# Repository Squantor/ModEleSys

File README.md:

# ModEleSys
This repository contains a modular system for electronics projects. It encompasses a backplane of which a few variants exist. Next to that there are various modules that are plugged into this backplane. These modules are 4 by 5 cm in size and the current backplane can contain 4 of them in a 2 by 2 grid. 
These modules come in different sizes, a 1by1 module occupies just one spot on the backplane, the 2by1 and 1by2 module occupy two spots and are for larger projects. Hypothetically there would also be a 2by2 module also but if you have that, why do you need a backplane?
If you use stackable headers for the modules, in principle you could stack multiple modules on top of eachother.

There are various modules available with the following functions:

* Power supply in a few different variants
* Microcontroller boards in a few different variants

These are "generic" building blocks so they can be used in many different projects. Project specific modules usually are owned by the projects themselves. Below is a non exhaustive list of projects using this system:
* [Ultra pure oscillator](https://github.com/Squantor/Metrology/tree/master/electronics/oscillator_variant_2) and [notch filter](https://github.com/Squantor/Metrology/tree/master/electronics/notch_filter)

I intend to use this system for many projects I have in mind.

## Structure
* [electronics](electronics/README.md) contains all the electronic hardware
* [software](software/README.md) contains all the software used in the project. Mostly contains examples for the microcontroller boards using this system.
* [mechanical](mechanical/README.md) contains all the CAD drawings, mostly 3d printable objects.
* [documentation](documentation/README.md) contains more in depth information and examples using this system.
## Cloning
This repository makes extensive use of submodules, use ```git clone --recurse-submodules https://github.com/Squantor/generic_project_template.git``` to clone everything in one go.

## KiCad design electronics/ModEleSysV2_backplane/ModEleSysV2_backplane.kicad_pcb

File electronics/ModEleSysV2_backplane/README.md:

# 10 by 10 cm aluminium box backplane with 30 pin DIN41612 connectors
10 by 10 cm aluminium box backplane  capable of fitting 4 5*4cm modules
## TODO's
Still some things need to be done:
* Review with one night in between
* Production
* Assemble
* Test & characterise
* update Readme.md with pictures and BOM
## BOM
* Search on ebay/aliexpress for a 10 by 10 by 5 extruded aluminium box.
* Momentary push pull switch (Todo LCSC partnumber)
* Angled LED
* Miscellanious passives
## Pictures

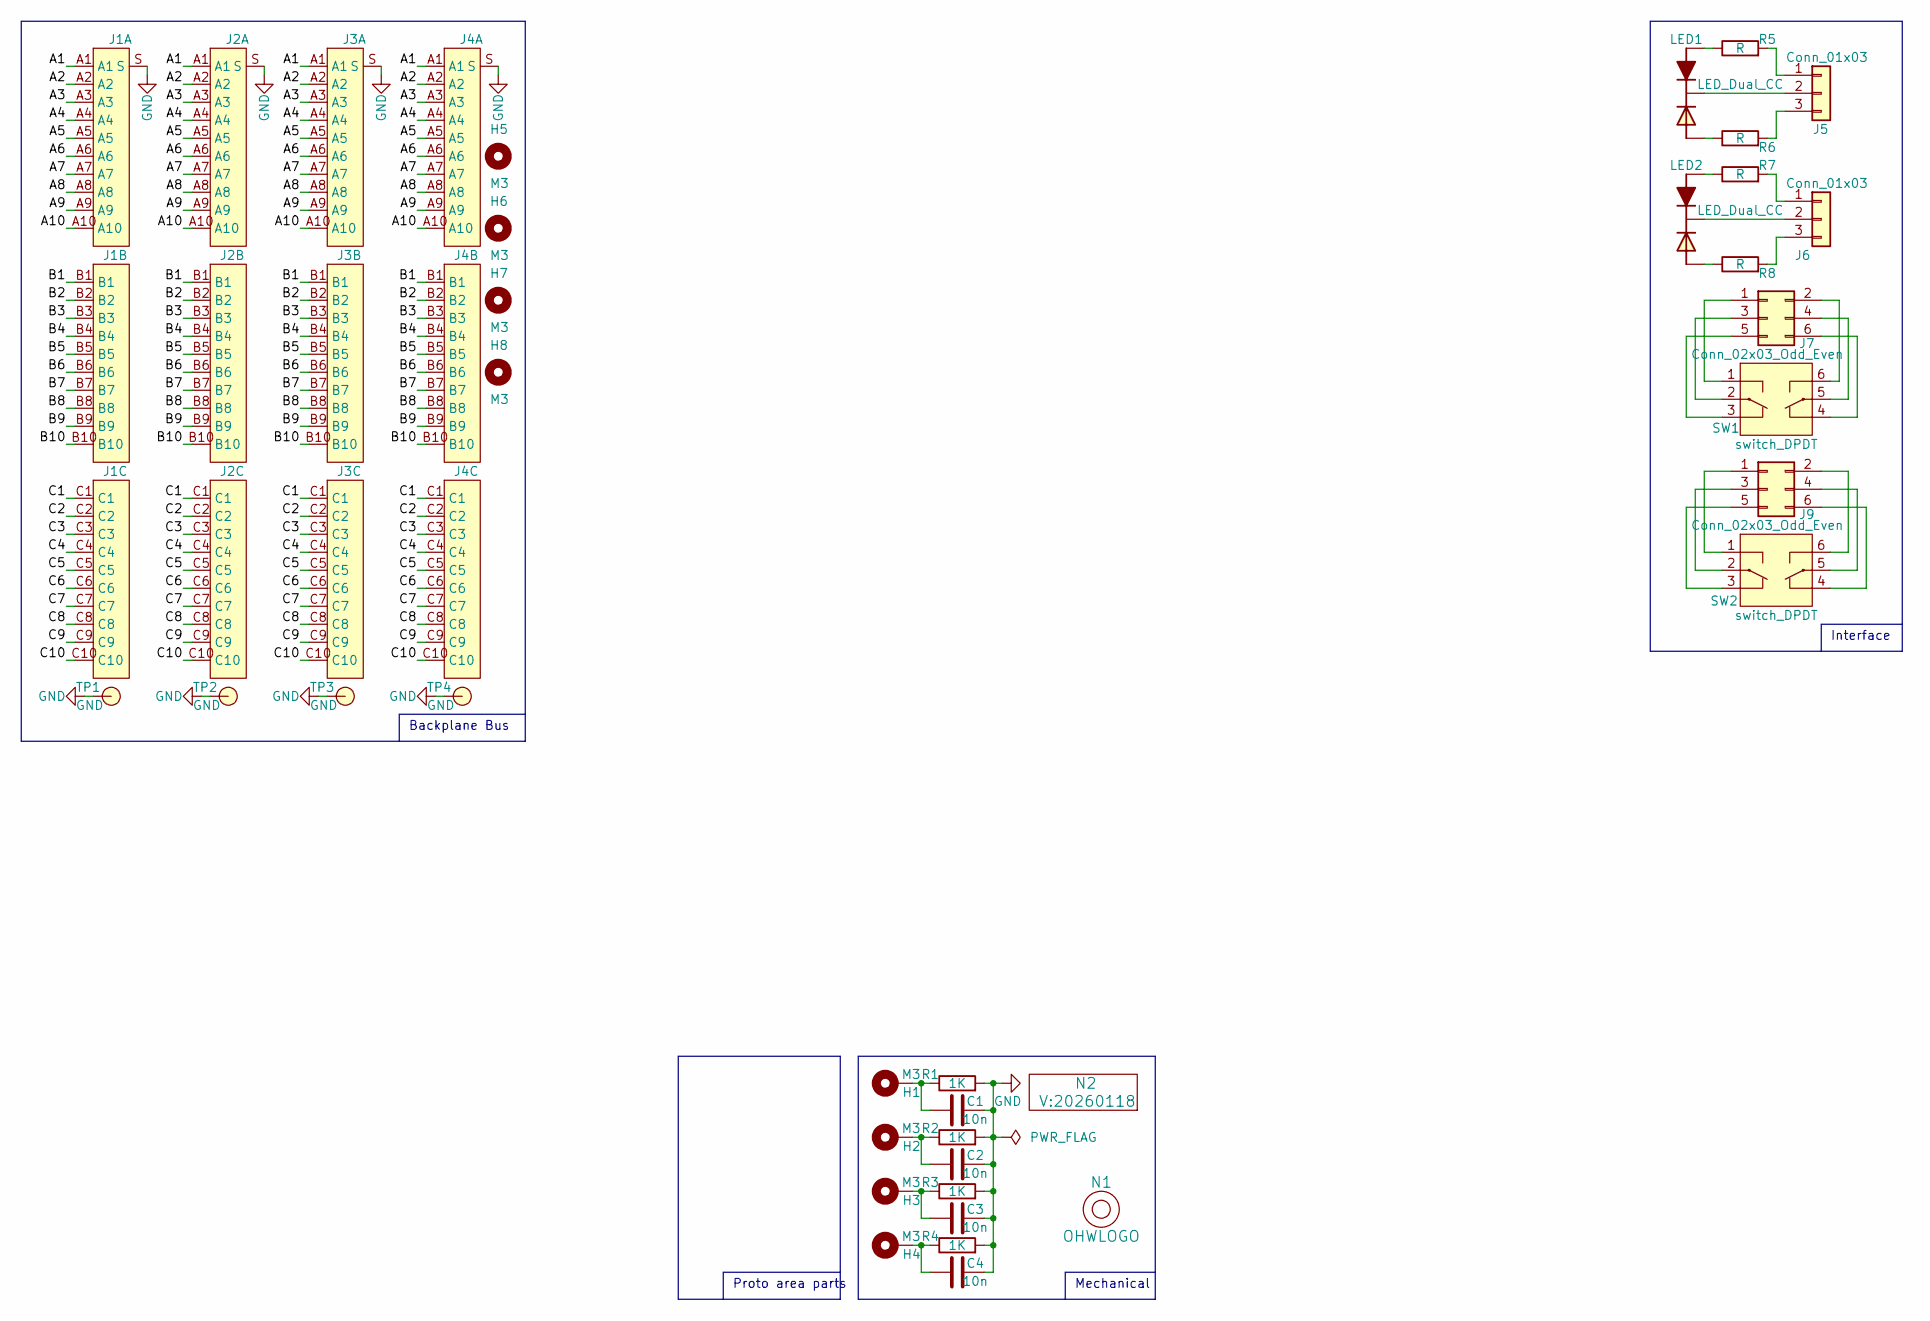
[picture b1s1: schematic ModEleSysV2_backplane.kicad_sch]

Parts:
C1, C2, C3, C4: 10n; C_0805+0603
H1, H2, H3, H4, H5, H6, H7, H8: M3; MountingHole_3.2mm_M3_Pad_Via
J1, J2, J3, J4: DIN41612_C3_3x10_Female_Vertical_THT_shields
J5, J6: Conn_01x03; JST_PH_B3B-PH-K_1x03_P2.00mm_Vertical
J7, J9: Conn_02x03_Odd_Even; DLL-XHY-6A
LED1, LED2: LED_Dual_CC; LED_DUAL_TH245_90deg
N1: OHWLOGO; OSHW-Symbol_6.7x6mm_SilkScreen
N2: V:20260118; Label_Generic
R1, R2, R3, R4: 1K; R_0805+0603
R5, R6, R7, R8: R; R_0603_hand
SW1, SW2: switch_DPDT; PS-22F02
TP1, TP2, TP3, TP4: GND; TestPoint_hole_H05R10

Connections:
/A1: J1.A1, J2.A1, J3.A1, J4.A1
/A2: J1.A2, J2.A2, J3.A2, J4.A2
/A3: J1.A3, J2.A3, J3.A3, J4.A3
/A4: J1.A4, J2.A4, J3.A4, J4.A4
/A5: J1.A5, J2.A5, J3.A5, J4.A5
/A6: J1.A6, J2.A6, J3.A6, J4.A6
/A7: J1.A7, J2.A7, J3.A7, J4.A7
/A8: J1.A8, J2.A8, J3.A8, J4.A8
/A9: J1.A9, J2.A9, J3.A9, J4.A9
/A10: J1.A10, J2.A10, J3.A10, J4.A10
/B1: J1.B1, J2.B1, J3.B1, J4.B1
/B2: J1.B2, J2.B2, J3.B2, J4.B2
/B3: J1.B3, J2.B3, J3.B3, J4.B3
/B4: J1.B4, J2.B4, J3.B4, J4.B4
/B5: J1.B5, J2.B5, J3.B5, J4.B5
/B6: J1.B6, J2.B6, J3.B6, J4.B6
/B7: J1.B7, J2.B7, J3.B7, J4.B7
/B8: J1.B8, J2.B8, J3.B8, J4.B8
/B9: J1.B9, J2.B9, J3.B9, J4.B9
/B10: J1.B10, J2.B10, J3.B10, J4.B10
/C1: J1.C1, J2.C1, J3.C1, J4.C1
/C2: J1.C2, J2.C2, J3.C2, J4.C2
/C3: J1.C3, J2.C3, J3.C3, J4.C3
/C4: J1.C4, J2.C4, J3.C4, J4.C4
/C5: J1.C5, J2.C5, J3.C5, J4.C5
/C6: J1.C6, J2.C6, J3.C6, J4.C6
/C7: J1.C7, J2.C7, J3.C7, J4.C7
/C8: J1.C8, J2.C8, J3.C8, J4.C8
/C9: J1.C9, J2.C9, J3.C9, J4.C9
/C10: J1.C10, J2.C10, J3.C10, J4.C10
GND: C1.2, C2.2, C3.2, C4.2, J1.S, J2.S, J3.S, J4.S, R1.2, R2.2, R3.2, R4.2, TP1.1, TP2.1, TP3.1, TP4.1
unnamed: C1.1, H1.1, R1.1
unnamed: C2.1, H2.1, R2.1
unnamed: C3.1, H3.1, R3.1
unnamed: C4.1, H4.1, R4.1
unnamed: J5.1, R5.2
unnamed: J5.2, LED1.2 (C)
unnamed: J5.3, R6.2
unnamed: J6.1, R7.2
unnamed: J6.2, LED2.2 (C)
unnamed: J6.3, R8.2
unnamed: J7.1, SW1.1 (SW1_P1)
unnamed: J7.2, SW1.6 (SW2_P2)
unnamed: J7.3, SW1.2 (SW1_C1)
unnamed: J7.4, SW1.5 (SW2_C1)
unnamed: J7.5, SW1.3 (SW1_P2)
unnamed: J7.6, SW1.4 (SW2_P2)
unnamed: J9.1, SW2.1 (SW1_P1)
unnamed: J9.2, SW2.6 (SW2_P2)
unnamed: J9.3, SW2.2 (SW1_C1)
unnamed: J9.4, SW2.5 (SW2_C1)
unnamed: J9.5, SW2.3 (SW1_P2)
unnamed: J9.6, SW2.4 (SW2_P2)
unnamed: LED1.1 (A1), R5.1
unnamed: LED1.3 (A2), R6.1
unnamed: LED2.1 (A1), R7.1
unnamed: LED2.3 (A2), R8.1

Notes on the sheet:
Proto area parts
Mechanical
Interface
Backplane Bus

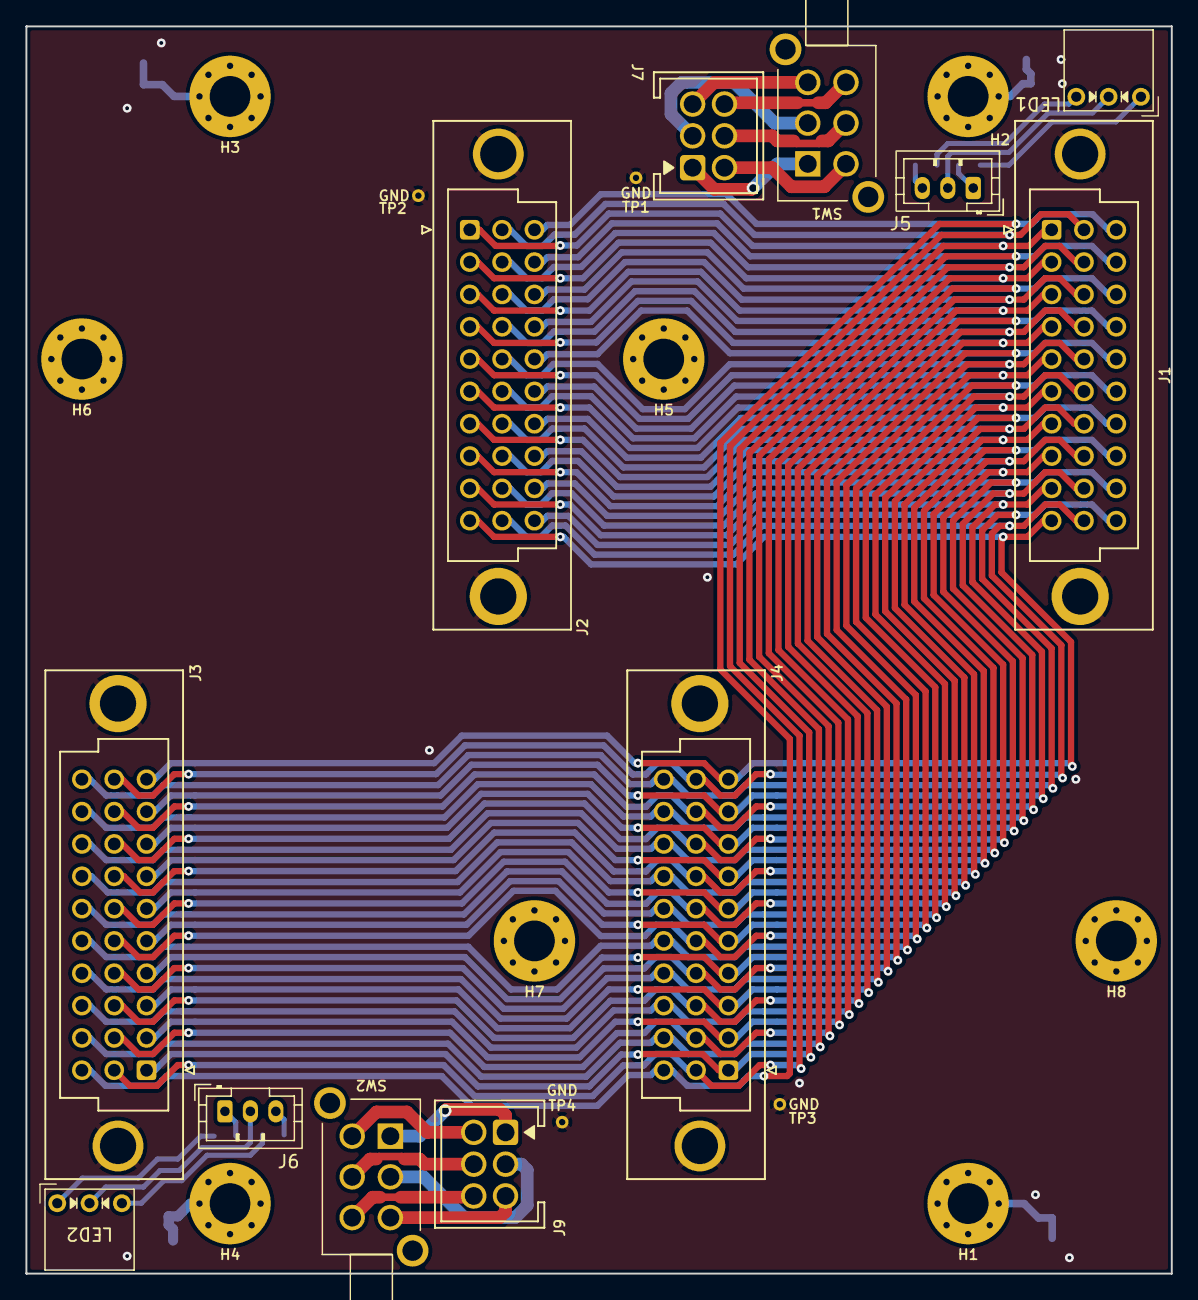
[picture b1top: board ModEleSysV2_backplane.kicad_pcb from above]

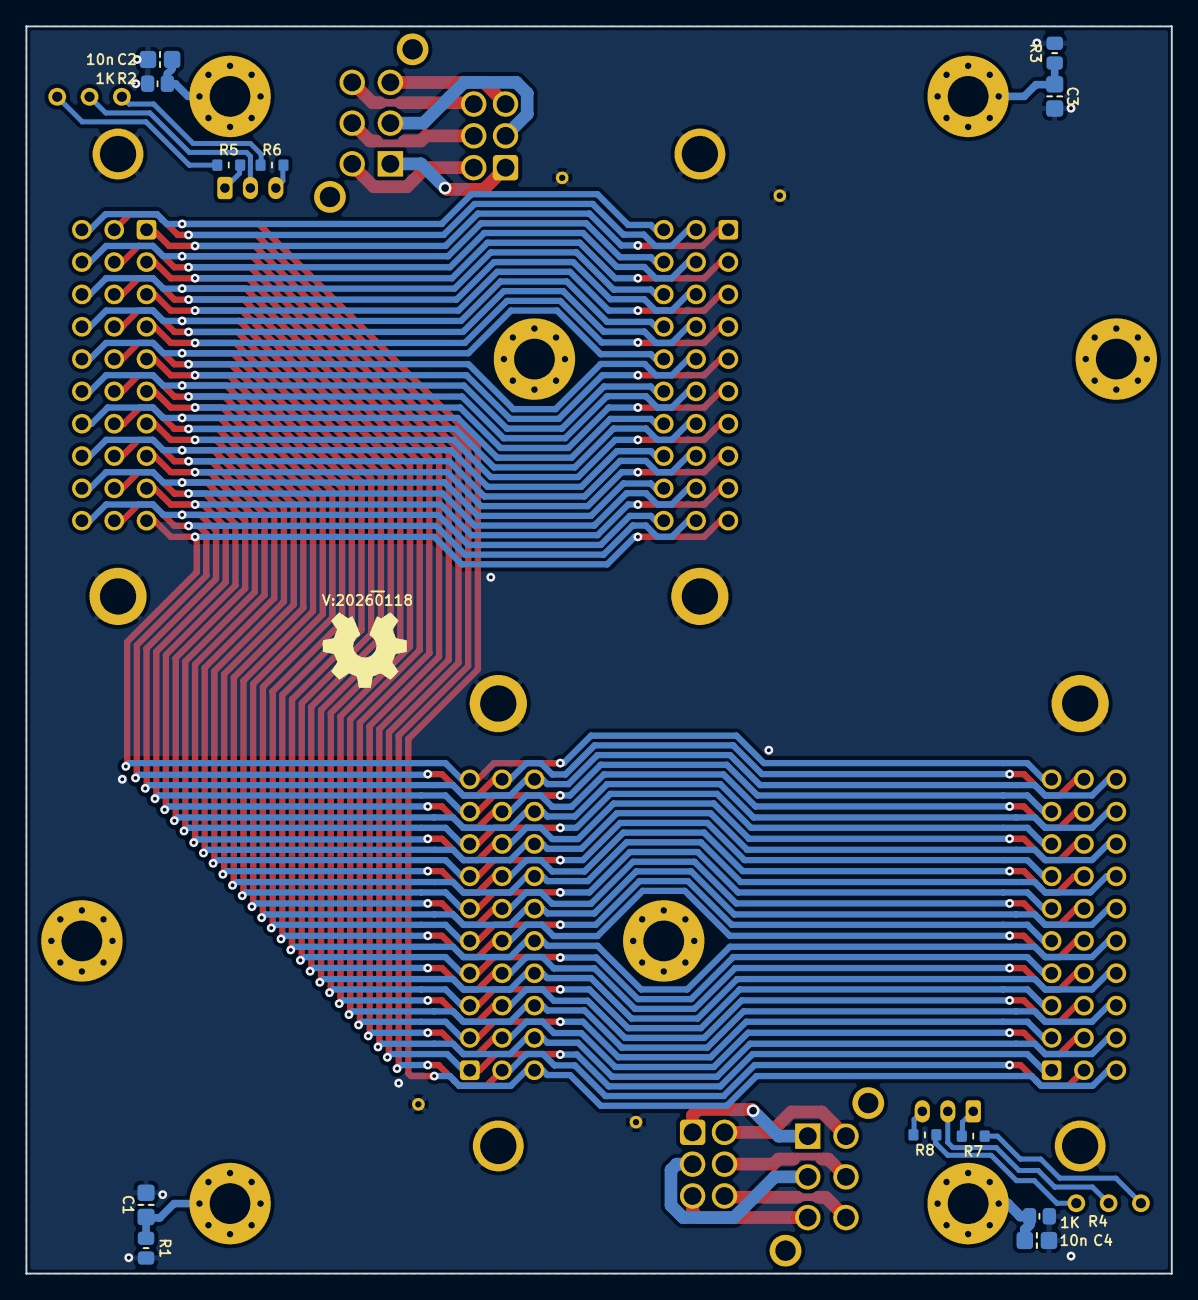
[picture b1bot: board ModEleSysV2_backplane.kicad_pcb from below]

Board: 2 copper layers, 90.0 x 98.0 mm, 38 parts (14 on the bottom side), 57 nets.

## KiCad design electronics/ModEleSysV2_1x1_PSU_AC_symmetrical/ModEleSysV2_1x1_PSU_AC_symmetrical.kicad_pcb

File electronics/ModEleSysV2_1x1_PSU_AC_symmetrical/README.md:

# ModEleSys V2 AC symmetrical powersupply project
This is a ModEleSys V2 module that takes an AC power input and changes this into symmetrical power on de +V and -V pins.
## TODO's
Still some things need to be done:
* Produce at Aisler/Oshpark/JLCPCB
* Assemble
* Test & characterise
* update Readme.md with pictures and BOM
## BOM
* D2PAK LM317/337
## Pictures
TODO

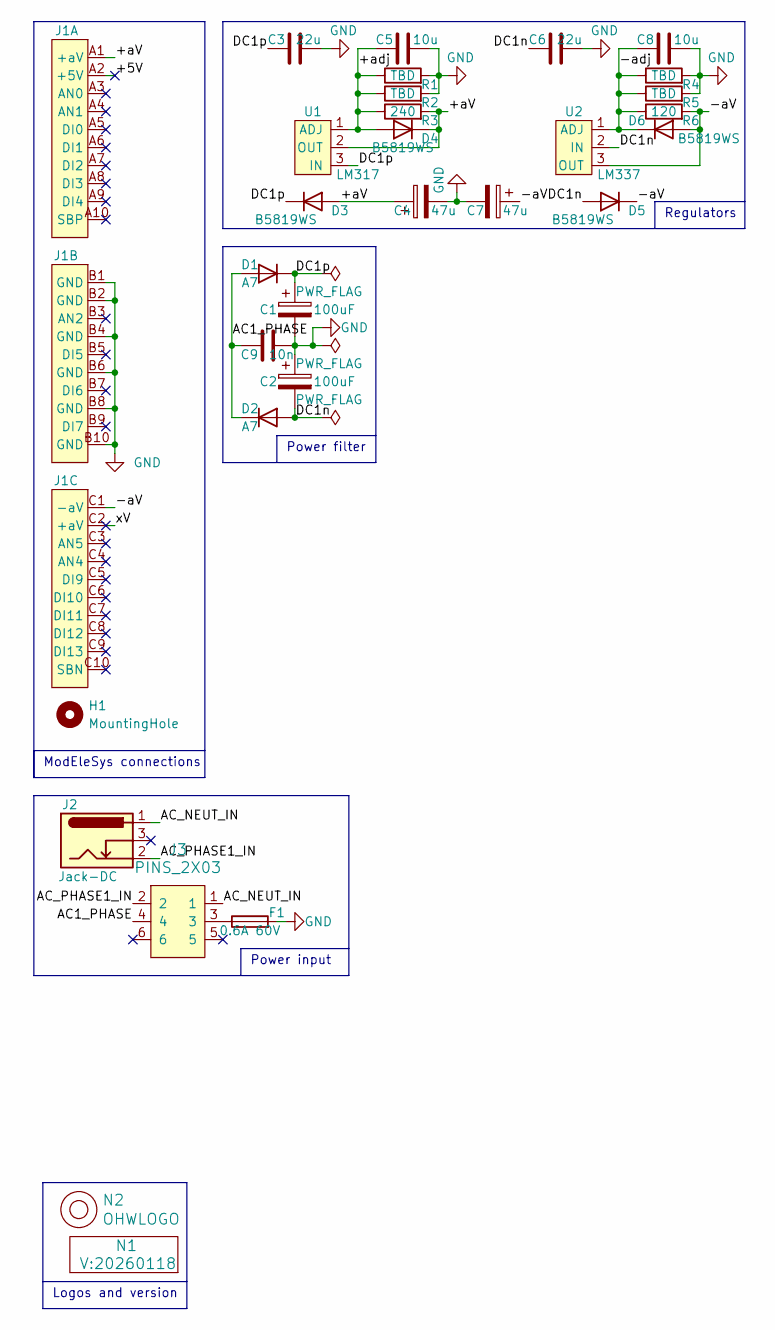
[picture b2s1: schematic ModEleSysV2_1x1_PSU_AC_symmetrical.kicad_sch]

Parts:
C1, C2: 100uF; C-050-100-elco-lying
C3, C6: 22u; C_1206_0805
C4, C7: 47u; C-025-065-elco
C5, C8: 10u; C_0805+0603
C9: 10n; C_0805+0603
D1, D2: A7; SOD-123F-hand
D3, D4, D5, D6: B5819WS; SOD-323-nexperia-hand
F1: 0.6A 60V; F_1812-bourns
H1: MountingHole; MountingHole_3.2mm_M3_Pad_Via
J1: DIN41612_R3_3x10_Male_Vertical_THT
J2: Jack-DC; BarrelJack_Horizontal_Holed
J3: PINS_2X03; DLL-XHY-6A
N1: V:20260118; Label_Generic
N2: OHWLOGO; OSHW-Symbol_6.7x6mm_SilkScreen
R1, R2, R4, R5: TBD; R_0805+0603
R3: 240; R_0805+0603
R6: 120; R_0805+0603
U1: LM317; SOT-223
U2: LM337; SOT-223

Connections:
/+5V: J1.A2 (+5V)
/+aV: C4.1, D3.2 (A), D4.1 (K), J1.A1 (+aV), R3.2, U1.2 (OUT)
/+adj: C5.1, D4.2 (A), R1.1, R2.1, R3.1, U1.1 (ADJ)
/-aV: C7.1, D5.1 (K), D6.2 (A), J1.C1 (-aV), R6.2, U2.3 (OUT)
/-adj: C8.1, D6.1 (K), R4.1, R5.1, R6.1, U2.1 (ADJ)
/AC1_PHASE: C9.1, D1.2 (A), D2.1 (K), J3.4
/AC_NEUT_IN: J2.1, J3.1
/AC_PHASE1_IN: J2.2, J3.2
/DC1n: C2.2, C6.1, D2.2 (A), D5.2 (A), U2.2 (IN)
/DC1p: C1.1, C3.1, D1.1 (K), D3.1 (K), U1.3 (IN)
/xV: J1.C2 (+aV)
GND: C1.2, C2.1, C3.2, C4.2, C5.2, C6.2, C7.2, C8.2, C9.2, F1.2, J1.B1 (GND), J1.B2 (GND), J1.B4 (GND), J1.B6 (GND), J1.B8 (GND), J1.B10 (GND), R1.2, R2.2, R4.2, R5.2
unnamed: F1.1, J3.3

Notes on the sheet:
ModEleSys connections
Logos and version
Power filter
Power input
Regulators

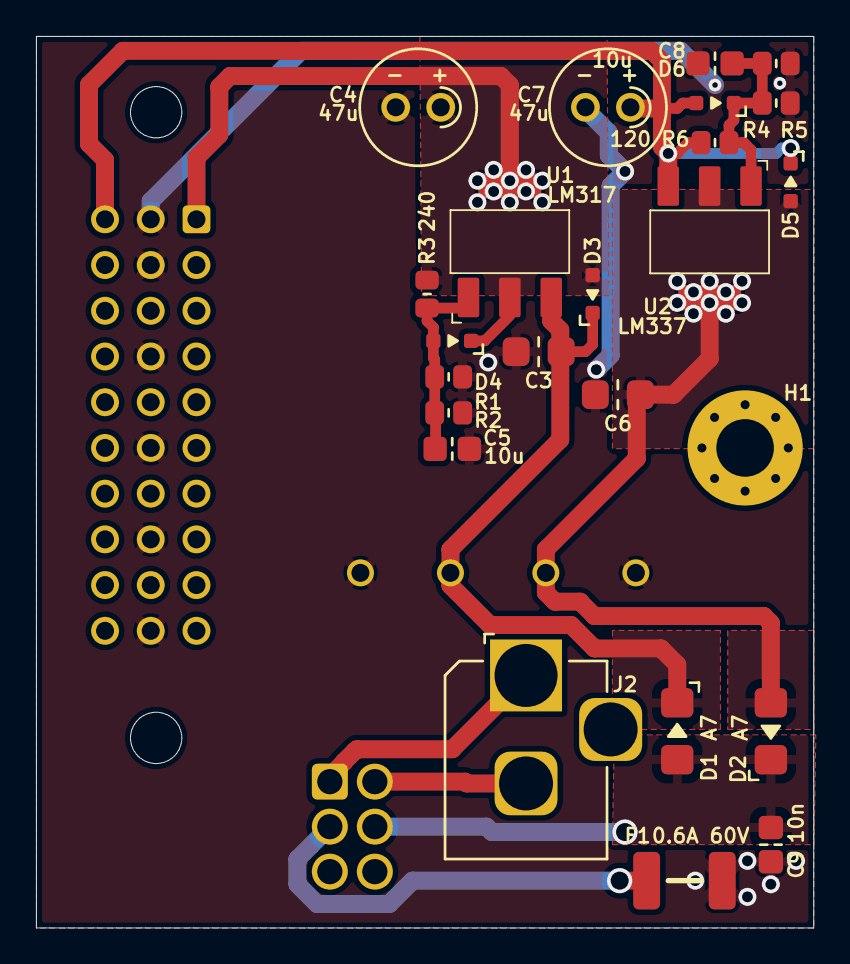
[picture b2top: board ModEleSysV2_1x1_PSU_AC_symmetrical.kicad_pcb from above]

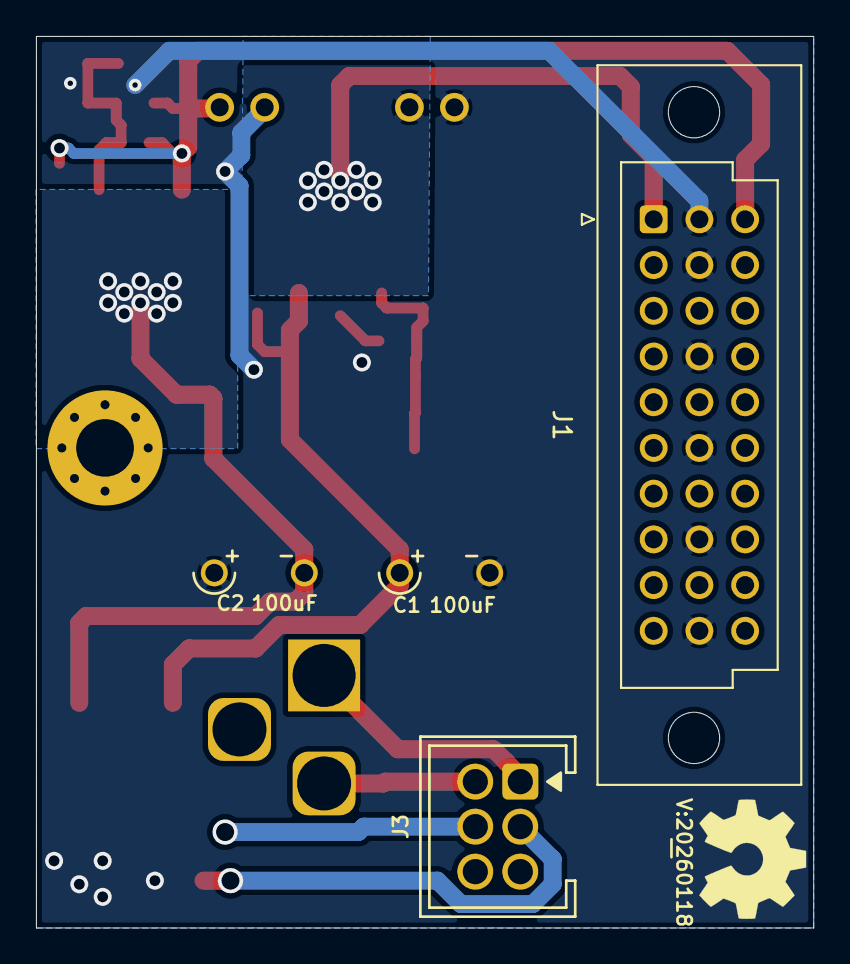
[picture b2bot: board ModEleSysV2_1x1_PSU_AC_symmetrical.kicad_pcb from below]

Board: 2 copper layers, 43.2 x 49.5 mm, 30 parts (6 on the bottom side), 11 nets.

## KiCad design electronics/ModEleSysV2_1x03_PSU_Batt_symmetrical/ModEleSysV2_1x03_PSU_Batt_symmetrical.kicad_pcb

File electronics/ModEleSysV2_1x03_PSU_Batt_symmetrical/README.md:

# ModEleSys V2 battery powersupply
Project description goes here.
## TODO's
Still some things need to be done:
* Review with one night in between
* Produce
* Assemble
* Test & characterise
* update Readme.md with pictures and BOM

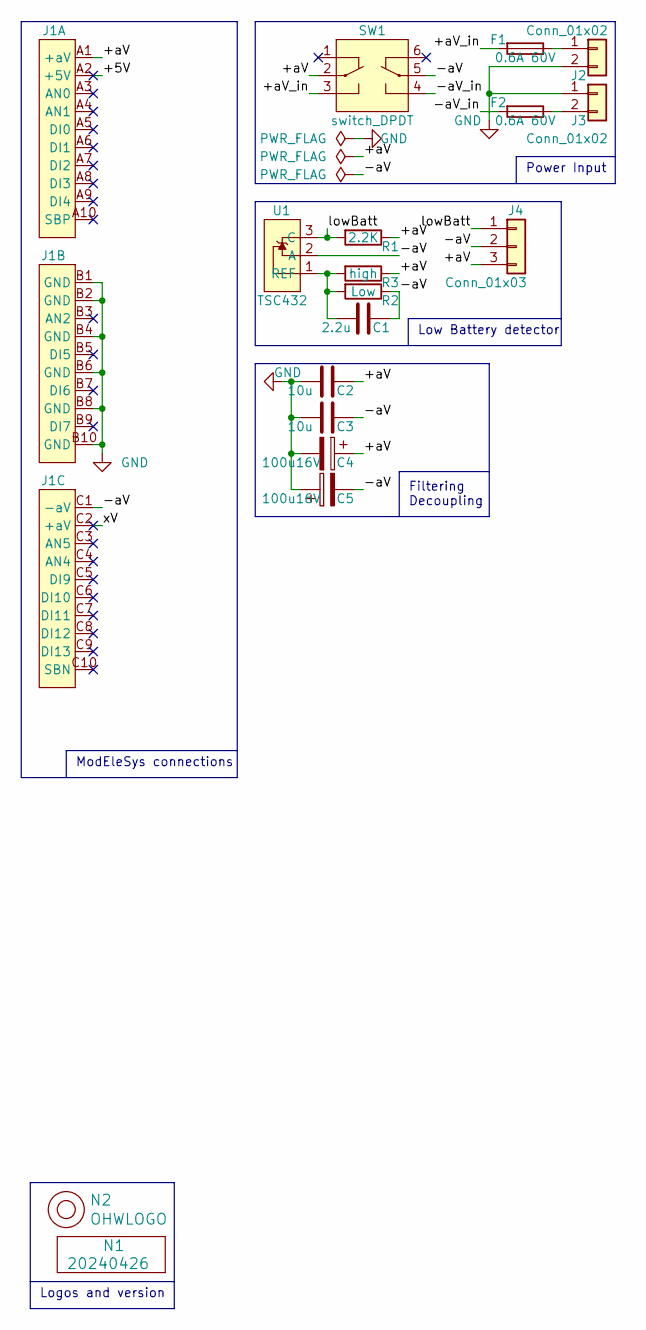
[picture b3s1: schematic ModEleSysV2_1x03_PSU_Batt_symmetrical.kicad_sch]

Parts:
C1: 2.2u; C_0805
C2, C3: 10u; C_1206_0805
C4, C5: 100u16V; C-025-065-elco
F1, F2: 0.6A 60V; F_1812-bourns
J1: DIN41612_R3_3x10_Male_Vertical_THT
J2, J3: Conn_01x02; JST_XH_B2B-XH-A_1x02_P2.50mm_Vertical
J4: Conn_01x03; JST_PH_B3B-PH-K_1x03_P2.00mm_Vertical
N1: 20240426; Label_Generic
N2: OHWLOGO; OSHW-Symbol_6.7x6mm_SilkScreen
R1: 2.2K; R_0603_hand
R2: Low; R_0603_hand
R3: high; R_0603_hand
SW1: switch_DPDT; PS-22F02
U1: TSC432; TO-92L_Inline_Wide

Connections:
/+5V: J1.A2 (+5V)
/+aV: C2.2, C4.1, J1.A1 (+aV), J4.3, R1.1, R3.1, SW1.2 (SW1_C1)
/+aV_in: F1.2, SW1.3 (SW1_P2)
/-aV: C1.2, C3.2, C5.2, J1.C1 (-aV), J4.2, R2.1, SW1.5 (SW2_C1), U1.2 (A)
/-aV_in: F2.2, SW1.4 (SW2_P2)
/lowBatt: J4.1, R1.2, U1.3 (C)
/xV: J1.C2 (+aV)
GND: C2.1, C3.1, C4.2, C5.1, J1.B1 (GND), J1.B2 (GND), J1.B4 (GND), J1.B6 (GND), J1.B8 (GND), J1.B10 (GND), J2.2, J3.1
unnamed: F1.1, J2.1
unnamed: F2.1, J3.2
unnamed: C1.1, R2.2, R3.2, U1.1 (REF)

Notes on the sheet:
ModEleSys connections
Logos and version
Power Input
Filtering Decoupling
Low Battery detector

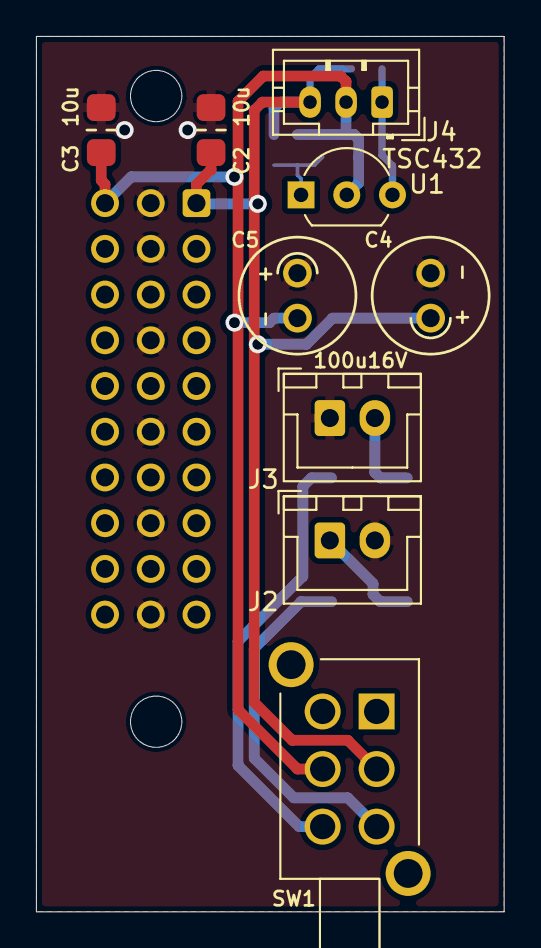
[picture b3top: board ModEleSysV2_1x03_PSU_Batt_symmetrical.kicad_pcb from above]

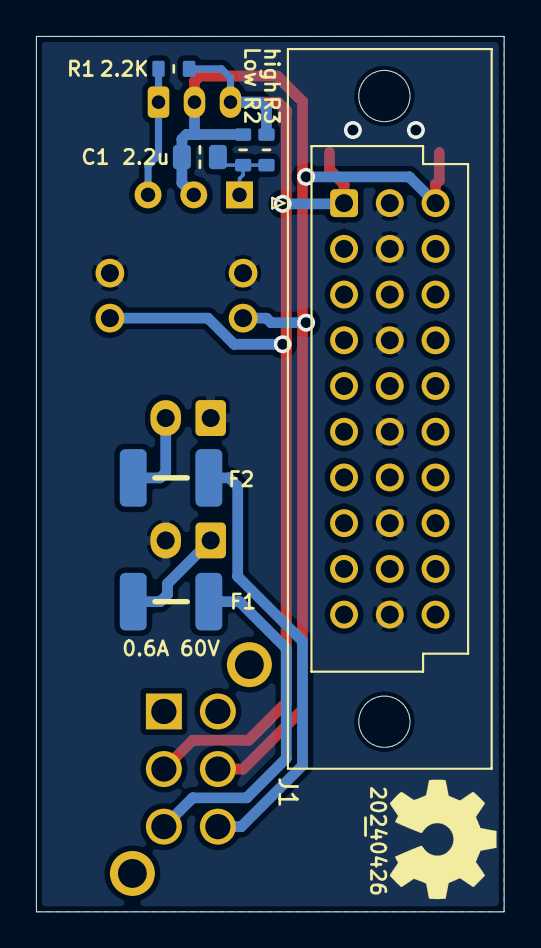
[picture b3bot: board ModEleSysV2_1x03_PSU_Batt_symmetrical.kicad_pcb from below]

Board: 2 copper layers, 26.0 x 48.6 mm, 18 parts (9 on the bottom side), 9 nets.

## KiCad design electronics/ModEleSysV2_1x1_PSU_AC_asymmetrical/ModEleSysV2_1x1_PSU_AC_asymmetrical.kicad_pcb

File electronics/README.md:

# ModEleSys electronics
The backplanes and modules of the ModEleSys are stored here.
Backplanes are prefixed with ```bp``` and some extra description.
Mmodules are prefixed with ```mod``` and size in the form of ```?x?``` where ? would be the size indicator. For example ```mod_1x1_symmetric_powersupply``` is a module of 1x1 that contains a symmetric powersupply.
## Backplanes
* [Passive backplane](bp_passive_10x10_alubox/README.md) with power switches and LED's
## Modules
* [symmetrical powersupply](mod_1x1_PSU_2xAC_flexible/README.md) using AC power input, two AC inputs available for symmetrical or unsymmetrical.
* 1x1 symmetrical powersupply using DC power input
* 1x2 low power symmetrical powersupply using 9V batteries
* LPC812 microcontroller board
* STM32G031 microcontroller board

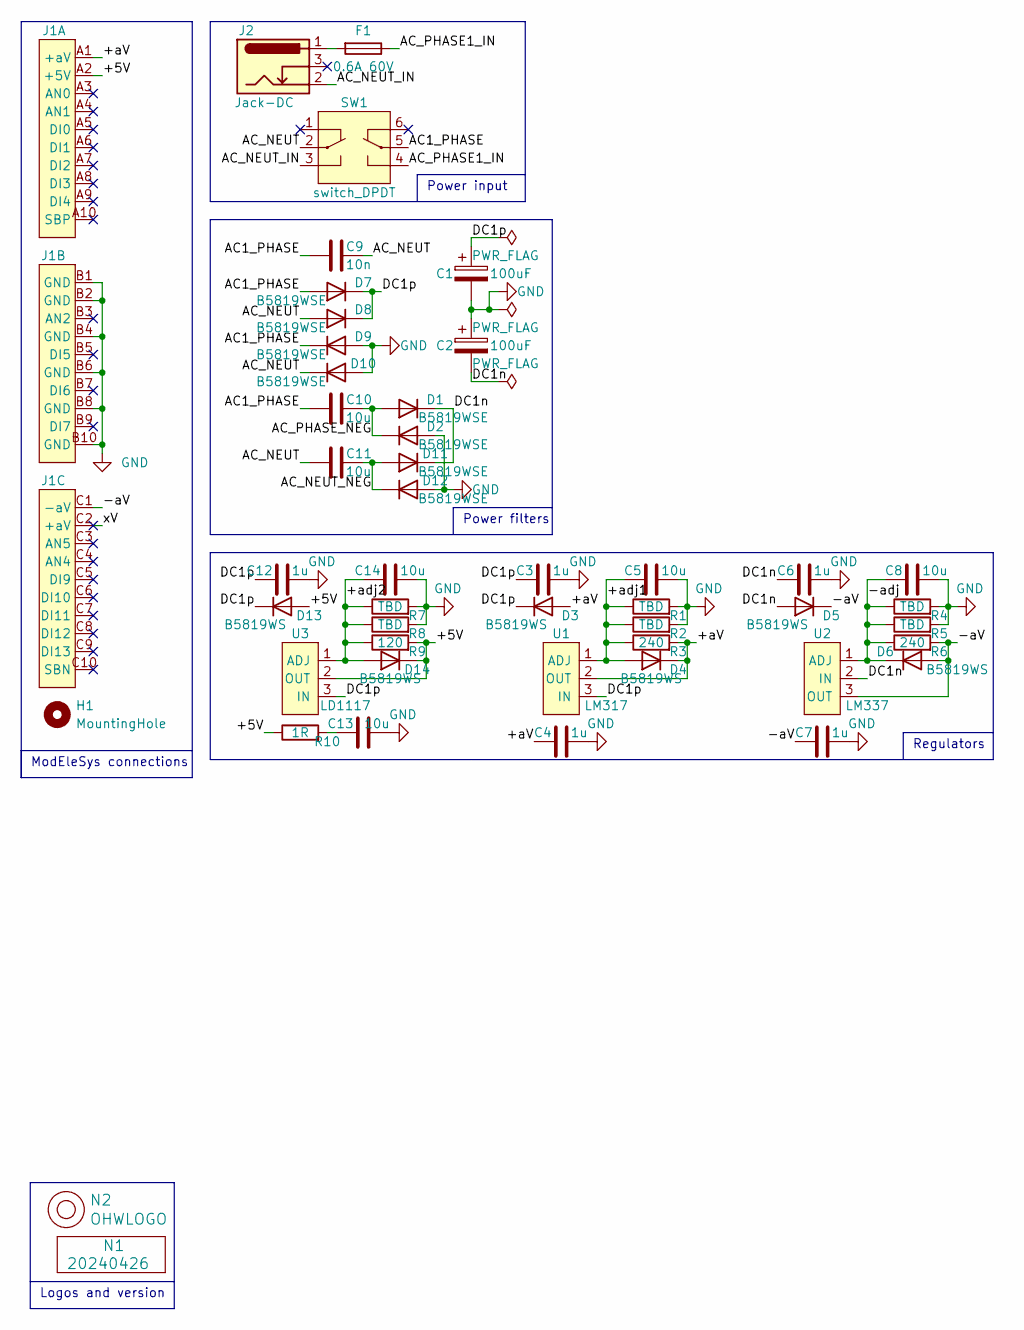
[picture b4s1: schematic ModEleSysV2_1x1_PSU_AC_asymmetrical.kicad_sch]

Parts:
C1, C2: 100uF; C-050-100-elco-lying
C3, C6, C12: 1u; C_0805+0603
C4, C7: 1u; C_1206_0805
C5, C8, C10, C11, C14: 10u; C_0805+0603
C9: 10n; C_0805+0603
C13: 10u; C_1206_0805
D1, D2, D7, D8, D9, D10, D11, D12: B5819WSE; SOD-323HE-shikues
D3, D4, D5, D6, D13, D14: B5819WS; SOD-323HE-shikues
F1: 0.6A 60V; F_1812-bourns
H1: MountingHole; MountingHole_3.2mm_M3_Pad_Via
J1: DIN41612_R3_3x10_Male_Vertical_THT
J2: Jack-DC; BarrelJack_Horizontal_Holed
N1: 20240426; Label_Generic
N2: OHWLOGO; OSHW-Symbol_6.7x6mm_SilkScreen
R1, R2, R4, R5, R7, R8: TBD; R_0603_hand
R3, R6: 240; R_0603_hand
R9: 120; R_0603_hand
R10: 1R; R_0603_hand
SW1: switch_DPDT; PS-22F02
U1: LM317; TO-252_D-PAK_IRF
U2: LM337; TO-252_D-PAK_IRF
U3: LD1117; TO-252_D-PAK_IRF

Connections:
/+5V: D13.2 (A), D14.1 (K), J1.A2 (+5V), R9.2, R10.1, U3.2 (OUT)
/+aV: C4.1, D3.2 (A), D4.1 (K), J1.A1 (+aV), R3.2, U1.2 (OUT)
/+adj1: C5.1, D4.2 (A), R1.1, R2.1, R3.1, U1.1 (ADJ)
/+adj2: C14.1, D14.2 (A), R7.1, R8.1, R9.1, U3.1 (ADJ)
/-aV: C7.1, D5.1 (K), D6.2 (A), J1.C1 (-aV), R6.2, U2.3 (OUT)
/-adj: C8.1, D6.1 (K), R4.1, R5.1, R6.1, U2.1 (ADJ)
/AC1_PHASE: C9.2, C10.2, D7.2 (A), D9.1 (K), SW1.5 (SW2_C1)
/AC_NEUT: C9.1, C11.2, D8.2 (A), D10.1 (K), SW1.2 (SW1_C1)
/AC_NEUT_IN: J2.2, SW1.3 (SW1_P2)
/AC_NEUT_NEG: C11.1, D11.2 (A), D12.1 (K)
/AC_PHASE1_IN: F1.1, SW1.4 (SW2_P2)
/AC_PHASE_NEG: C10.1, D1.2 (A), D2.1 (K)
/DC1n: C2.2, C6.1, D1.1 (K), D5.2 (A), D11.1 (K), U2.2 (IN)
/DC1p: C1.1, C3.1, C12.1, D3.1 (K), D7.1 (K), D8.1 (K), D13.1 (K), U1.3 (IN), U3.3 (IN)
/xV: J1.C2 (+aV)
GND: C1.2, C2.1, C3.2, C4.2, C5.2, C6.2, C7.2, C8.2, C12.2, C13.2, C14.2, D2.2 (A), D9.2 (A), D10.2 (A), D12.2 (A), J1.B1 (GND), J1.B2 (GND), J1.B4 (GND), J1.B6 (GND), J1.B8 (GND), J1.B10 (GND), R1.2, R2.2, R4.2, R5.2, R7.2, R8.2
unnamed: C13.1, R10.2
unnamed: F1.2, J2.1

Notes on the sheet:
ModEleSys connections
Logos and version
Power filters
Power input
Regulators

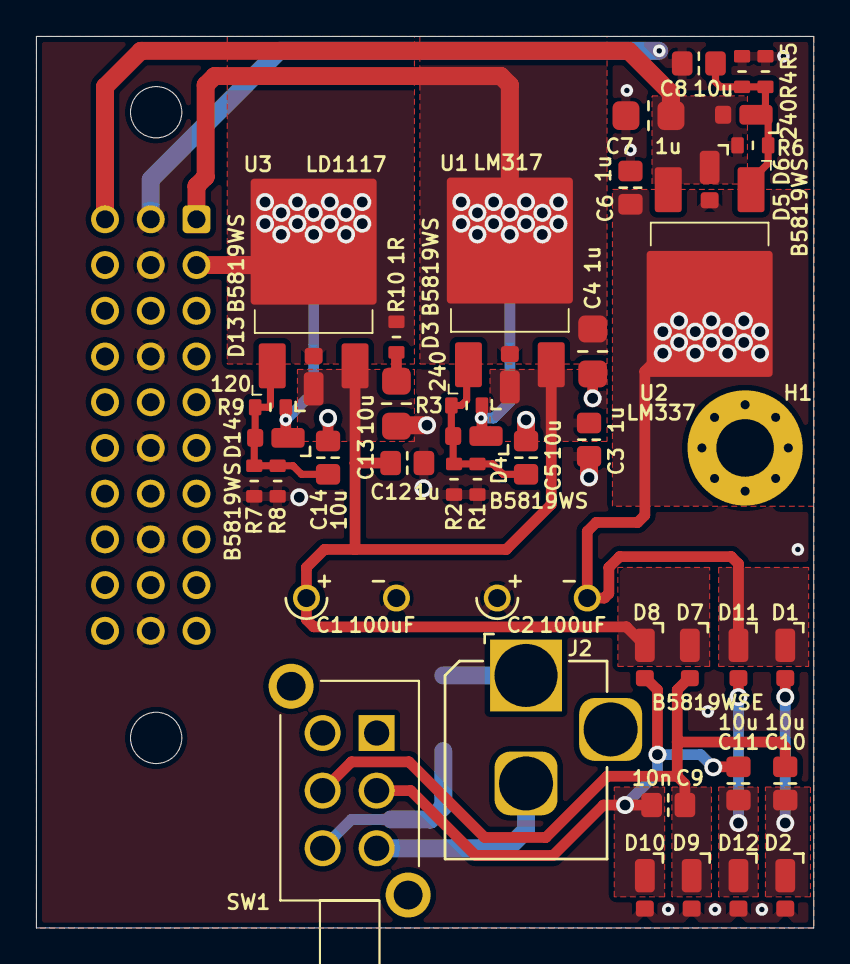
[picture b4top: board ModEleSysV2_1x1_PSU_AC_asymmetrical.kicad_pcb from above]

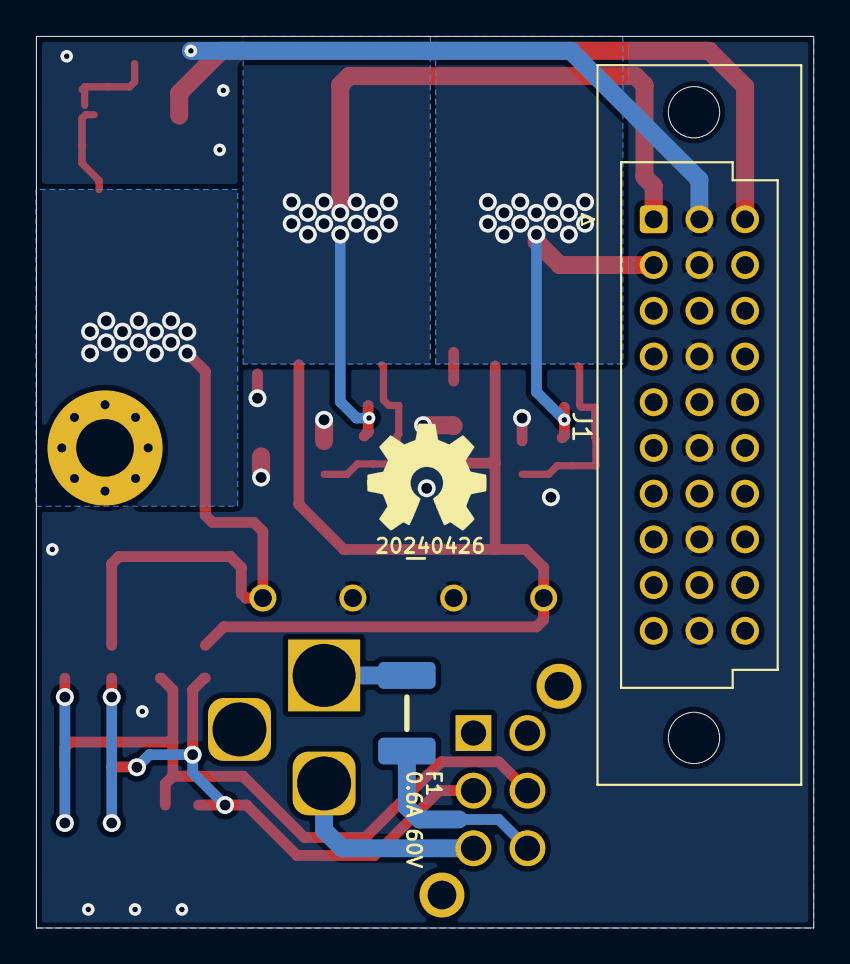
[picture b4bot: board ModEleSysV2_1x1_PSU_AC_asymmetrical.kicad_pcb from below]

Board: 2 copper layers, 43.2 x 49.5 mm, 48 parts (4 on the bottom side), 17 nets.

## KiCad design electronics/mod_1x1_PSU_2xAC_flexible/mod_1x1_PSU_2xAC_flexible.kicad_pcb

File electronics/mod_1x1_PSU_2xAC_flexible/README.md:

# ModEleSys
ModEleSys 1x1 module Powersupply. Two AC inputs: one for a symmetrical powersupply and one for a single ended powersupply. Symmetric powersupply accepts LM317/LM337 regulators. Single ended supply has footprints for a LM317 regulator and LM78XX style regulators. All regulators are TO220 with a small heatsink. Due to limited space for capacitance the amount of current is also limited.
## TODO's
Still some things need to be done:
* Assemble
* Test & characterise
* update Readme.md with pictures and BOM
## BOM
This is a list of hardware components. If just mentioned a generic component like a 1K 0402 resistor, just name it as such, free to substitute. If you need some special integrated IC's show some sources like Mouser, Digikey, Farnell, or LCSC
* TO220 LM317, LM337, LM78XX style regulator
* SMA cased diodes
* Very skinny capacitors but substitute for your own
* 500mA trip polyfuses in 1812 SMT housing

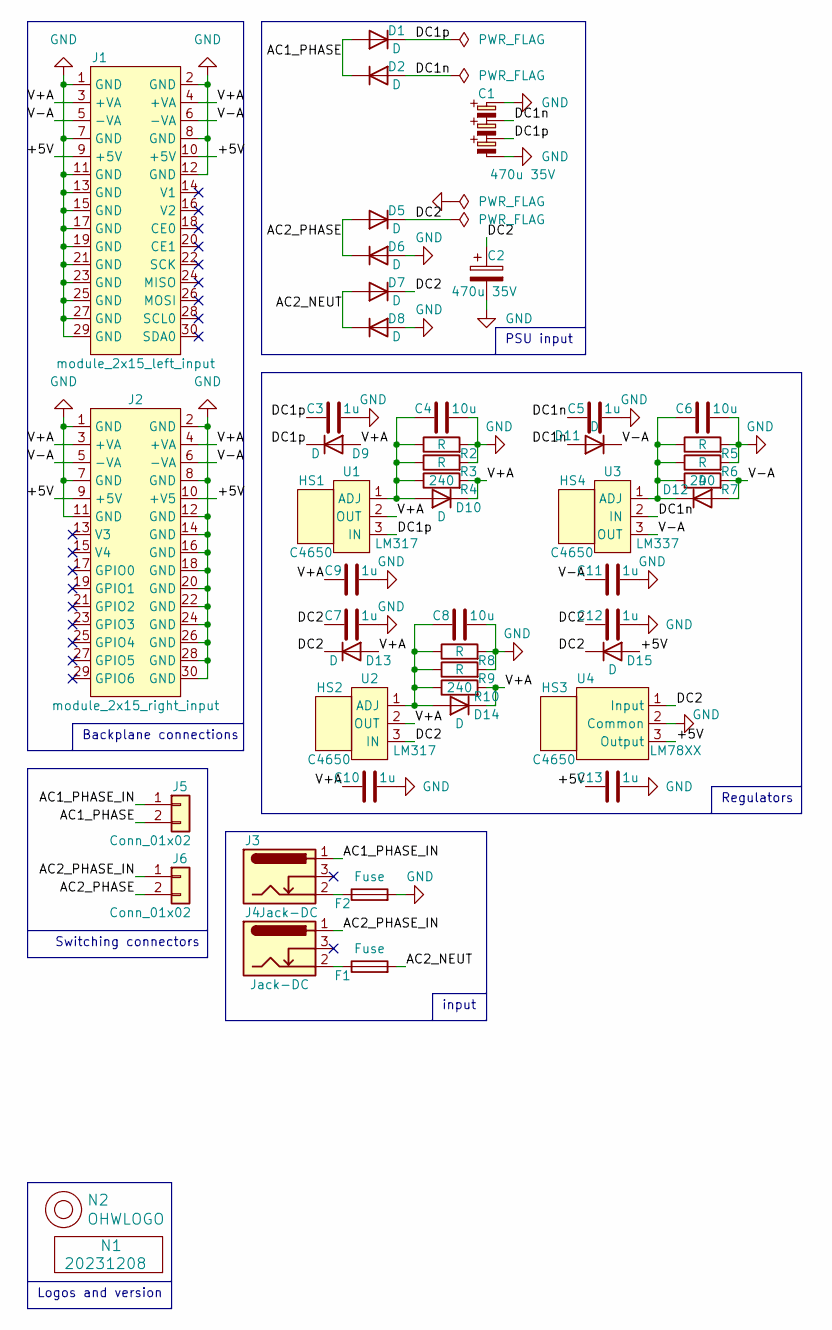
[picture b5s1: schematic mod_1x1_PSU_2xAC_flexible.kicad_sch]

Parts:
C1: 470u 35V; Cx3-035-080-elco
C2: 470u 35V; C-035-080-elco
C3, C5, C7, C9, C10, C11, C12, C13: 1u; C_0805+0603
C4, C6, C8: 10u; C_0805+0603
D1, D2, D5, D6, D7, D8, D9, D11, D13, D15: D; SOD-123F-hand
D10, D12, D14: D; SOD-323-nexperia-hand
F1, F2: Fuse; F_1812-bourns
HS1, HS2, HS3, HS4: C4650; XSD_C4650
J1: module_2x15_left_input; module_2x15_left
J2: module_2x15_right_input; module_2x15_right
J3, J4: Jack-DC; BarrelJack_Horizontal_Holed
J5, J6: Conn_01x02; JST_PH_B2B-PH-K_1x02_P2.00mm_Vertical
N1: 20231208; Label_Generic
N2: OHWLOGO; OSHW-Symbol_6.7x6mm_SilkScreen
R2, R3, R5, R6, R8, R9: R; R_0805+0603
R4, R7, R10: 240; R_0805+0603
U1, U2: LM317; TO-220-3_Vertical
U3: LM337; TO-220-3_Vertical
U4: LM78XX; TO-220-3_Vertical

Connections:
/+5V: C13.1, D15.2 (A), J1.9 (+5V), J1.10 (+5V), J2.9 (+5V), J2.10 (+V5), U4.3 (Output)
/AC1_PHASE: D1.2 (A), D2.1 (K), J5.2
/AC1_PHASE_IN: J3.1, J5.1
/AC2_NEUT: D7.2 (A), D8.1 (K), F1.2
/AC2_PHASE: D5.2 (A), D6.1 (K), J6.2
/AC2_PHASE_IN: J4.1, J6.1
/DC1n: C1.2, C5.1, D2.2 (A), D11.2 (A), U3.2 (IN)
/DC1p: C1.3, C3.1, D1.1 (K), D9.1 (K), U1.3 (IN)
/DC2: C2.1, C7.1, C12.1, D5.1 (K), D7.1 (K), D13.1 (K), D15.1 (K), U2.3 (IN), U4.1 (Input)
/V+A: C9.1, C10.1, D9.2 (A), D10.1 (K), D13.2 (A), D14.1 (K), J1.3 (+VA), J1.4 (+VA), J2.3 (+VA), J2.4 (+VA), R4.2, R10.2, U1.2 (OUT), U2.2 (OUT)
/V-A: C11.1, D11.1 (K), D12.2 (A), J1.5 (-VA), J1.6 (-VA), J2.5 (-VA), J2.6 (-VA), R7.2, U3.3 (OUT)
GND: C1.1, C1.4, C2.2, C3.2, C4.2, C5.2, C6.2, C7.2, C8.2, C9.2, C10.2, C11.2, C12.2, C13.2, D6.2 (A), D8.2 (A), F2.2, J1.1 (GND), J1.2 (GND), J1.7 (GND), J1.8 (GND), J1.11 (GND), J1.12 (GND), J1.13 (GND), J1.15 (GND), J1.17 (GND), J1.19 (GND), J1.21 (GND), J1.23 (GND), J1.25 (GND), J1.27 (GND), J1.29 (GND), J2.1 (GND), J2.2 (GND), J2.7 (GND), J2.8 (GND), J2.11 (GND), J2.12 (GND), J2.14 (GND), J2.16 (GND), J2.18 (GND), J2.20 (GND), J2.22 (GND), J2.24 (GND), J2.26 (GND), J2.28 (GND), J2.30 (GND), R2.2, R3.2, R5.2, R6.2, R8.2, R9.2, U4.2 (Common)
unnamed: C4.1, D10.2 (A), R2.1, R3.1, R4.1, U1.1 (ADJ)
unnamed: C6.1, D12.1 (K), R5.1, R6.1, R7.1, U3.1 (ADJ)
unnamed: C8.1, D14.2 (A), R8.1, R9.1, R10.1, U2.1 (ADJ)
unnamed: F1.1, J4.2
unnamed: F2.1, J3.2

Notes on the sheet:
Backplane connections
input
Logos and version
PSU input
Switching connectors
Regulators
